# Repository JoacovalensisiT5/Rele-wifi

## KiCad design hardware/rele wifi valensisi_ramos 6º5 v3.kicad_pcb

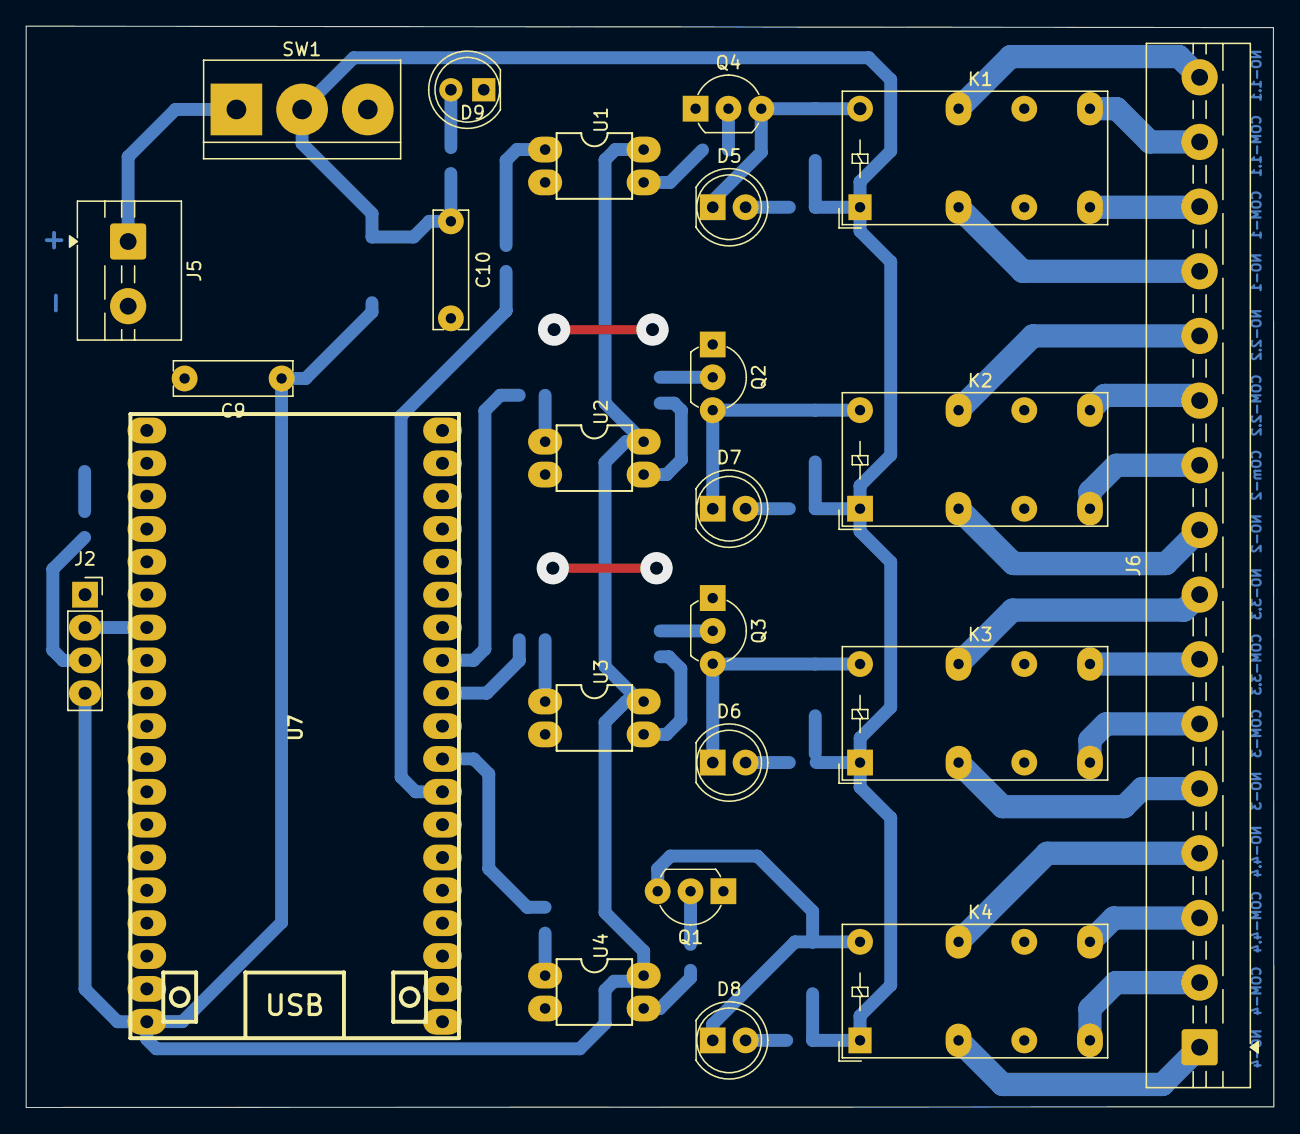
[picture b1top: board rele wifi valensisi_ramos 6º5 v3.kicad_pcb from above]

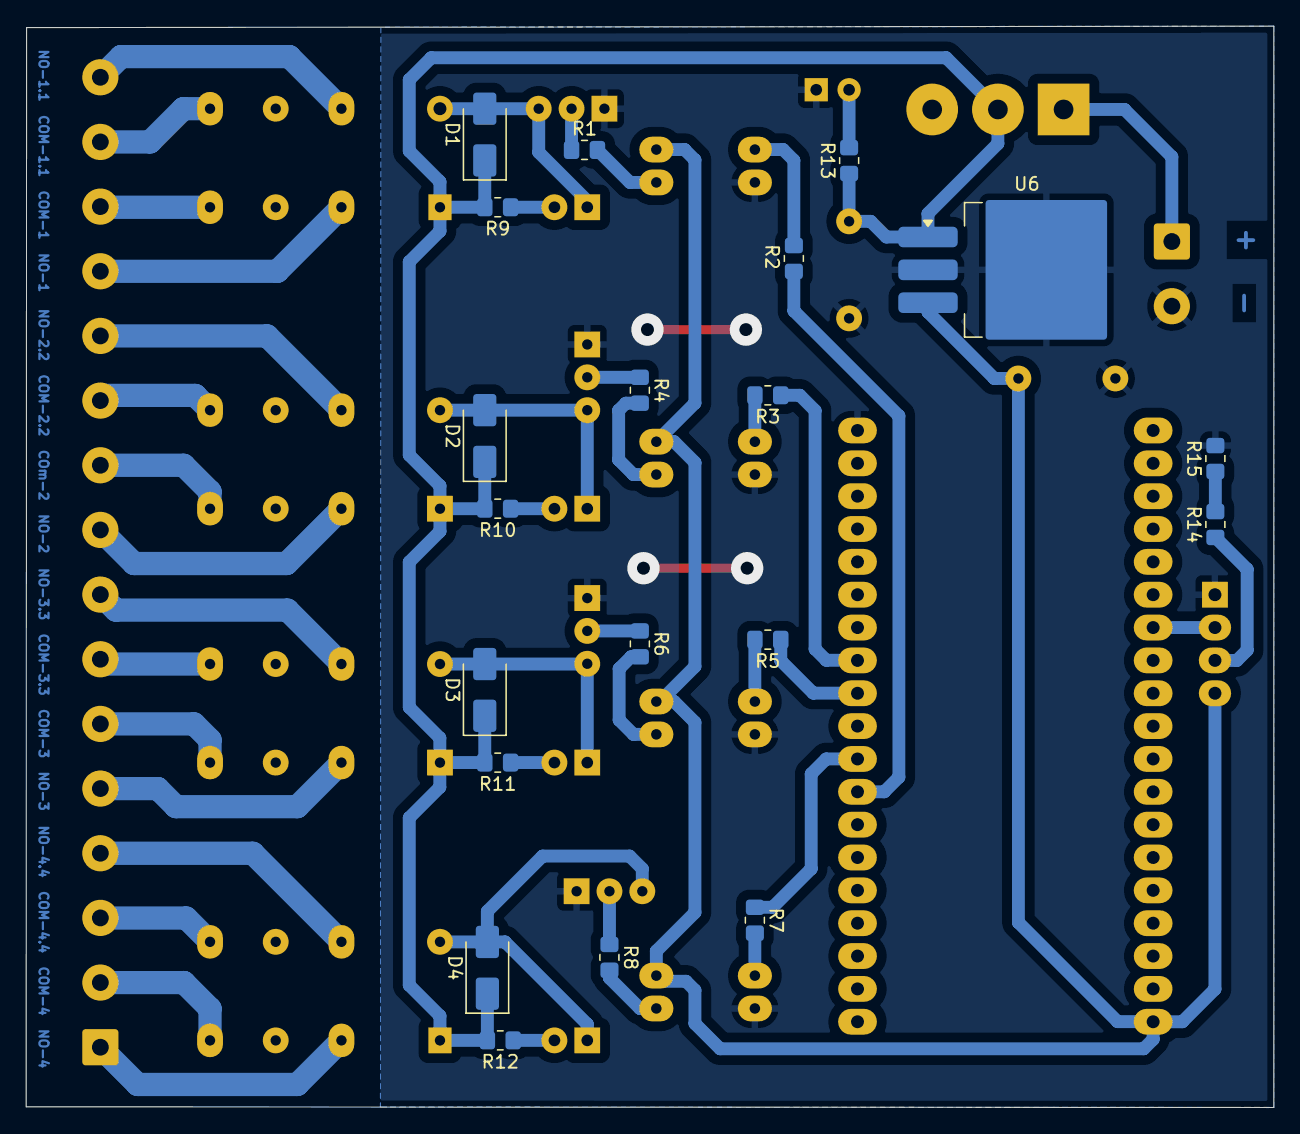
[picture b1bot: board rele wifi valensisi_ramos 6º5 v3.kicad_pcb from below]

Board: 2 copper layers, 96.5 x 83.6 mm, 44 parts (20 on the bottom side), 48 nets.

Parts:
C9: 0.1uf; C_Rect_L9.0mm_W2.5mm_P7.50mm_MKT
C10: 0.22uf; C_Rect_L9.0mm_W2.5mm_P7.50mm_MKT
D1, D2, D3, D4: 1N4007; D_SMA
D5, D6, D7, D8, D9: LED; LED_D5.0mm
J2: ultrasonido; PinSocket_1x04_P2.54mm_Vertical
J5: entrada; TerminalBlock_MaiXu_MX126-5.0-02P_1x02_P5.00mm
J6: Screw_Terminal_01x16; TerminalBlock_MaiXu_MX126-5.0-16P_1x16_P5.00mm
K1, K2, K3, K4: Relay_DPDT; Relay_DPDT_Finder_30.22
Q1, Q2, Q3: 2N2222; TO-92L_Inline_Wide
Q4: 2N2222; TO-92_Inline_Wide
R1, R4, R6, R8: 1K; R_0805_2012Metric_Pad1.20x1.40mm_HandSolder
R2, R3, R5, R7: 220; R_0805_2012Metric_Pad1.20x1.40mm_HandSolder
R9, R10, R11, R12, R13: 1k; R_0805_2012Metric_Pad1.20x1.40mm_HandSolder
R14: 1,2K; R_0805_2012Metric_Pad1.20x1.40mm_HandSolder
R15: 2,2K; R_0805_2012Metric_Pad1.20x1.40mm_HandSolder
SW1: SW_DPST_x2; TerminalBlock_bornier-3_P5.08mm
U1, U2, U3, U4: PC817; DIL04
U6: L7805; TO-263-3_TabPin2
U7: ESP32_DEVKITC; ESP32S

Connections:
+5V: C9.1, J2.4, U1.4, U2.4, U3.4, U4.4, U6.3 (OUT), U7.19 (5V)
+12V: C10.1, D1.1 (K), D2.1 (K), D3.1 (K), D4.1 (K), K1.A1, K2.A1, K3.A1, K4.A1, R9.2, R10.2, R11.2, R12.2, R13.1, SW1.2 (B), U6.1 (IN)
COM-1: J6.13, K1.11
COM-1.1: J6.16, K1.21
COM-2: J6.9, K2.11
COM-2.2: J6.12, K2.21
COM-3: J6.5, K3.11
COM-3.3: J6.8, K3.21
COM-4: J6.1, K4.11
COM-4.4: J6.4, K4.21
GND: C9.2, C10.2, D9.1 (K), J2.1, J5.2, Q1.1, Q2.1, Q3.1, Q4.1, R15.2, U1.2, U2.2, U3.2, U4.2, U6.2 (GND), U7.38 (GND)
NO-1: J6.14, K1.14
NO-1.1: J6.15, K1.24
NO-2: J6.10, K2.14
NO-2.2: J6.11, K2.24
NO-3: J6.6, K3.14
NO-3.3: J6.7, K3.24
NO-4: J6.2, K4.14
NO-4.4: J6.3, K4.24
unnamed: D1.2 (A), D5.1 (K), K1.A2, Q4.3
unnamed: D2.2 (A), D7.1 (K), K2.A2, Q2.3
unnamed: D3.2 (A), D6.1 (K), K3.A2, Q3.3
unnamed: D4.2 (A), D8.1 (K), K4.A2, Q1.3
unnamed: D5.2 (A), R9.1
unnamed: D6.2 (A), R11.1
unnamed: D7.2 (A), R10.1
unnamed: D8.2 (A), R12.1
unnamed: D9.2 (A), R13.2
unnamed: J5.1, SW1.1 (A)
unnamed: Q1.2, R8.1
unnamed: Q2.2, R4.1
unnamed: Q3.2, R6.1
unnamed: Q4.2, R1.1
unnamed: R1.2, U1.3
unnamed: R2.2, U1.1
unnamed: R3.2, U2.1
unnamed: R4.2, U2.3
unnamed: R5.2, U3.1
unnamed: R6.2, U3.3
unnamed: R7.2, U4.1
unnamed: R8.2, U4.3
P16: R2.1, U7.27 (IO16)
P17: R7.1, U7.28 (IO17)
P18: R5.1, U7.30 (IO18)
P19: R3.1, U7.31 (IO19)
d echo: R14.2, R15.1
echo: J2.3, R14.1
trig: J2.2, U7.7 (IO32)

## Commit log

2025-03-28 Mi primer commit
2025-03-28 Modificamos el titulodel index.html
2025-03-28 agregue carpetas
2025-05-13 Create Hardware
2025-05-13 Software
2025-06-06 Create software
2025-06-06 Create 3D
